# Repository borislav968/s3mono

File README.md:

# Устройство согласования ЭСУД SECU-3 c моновпрысками VAG

ЭСУД SECU-3 поддерживает использование регуляторов холостого хода на основе шагового привода или электромагнита (ШИМ). Моновпрыск Bosch, применявшийся на автомобилях VAG, использует регулятор на основе коллекторного электродвигателя с обратной связью по датчику положения дроссельной заслонки, и не имеет отдельного канала холостого хода.
Для управления этим регулятором, а также согласования сигнала положения дросселя, и предназначено это устройство. Также здесь есть драйвер низкоомной форсунки.

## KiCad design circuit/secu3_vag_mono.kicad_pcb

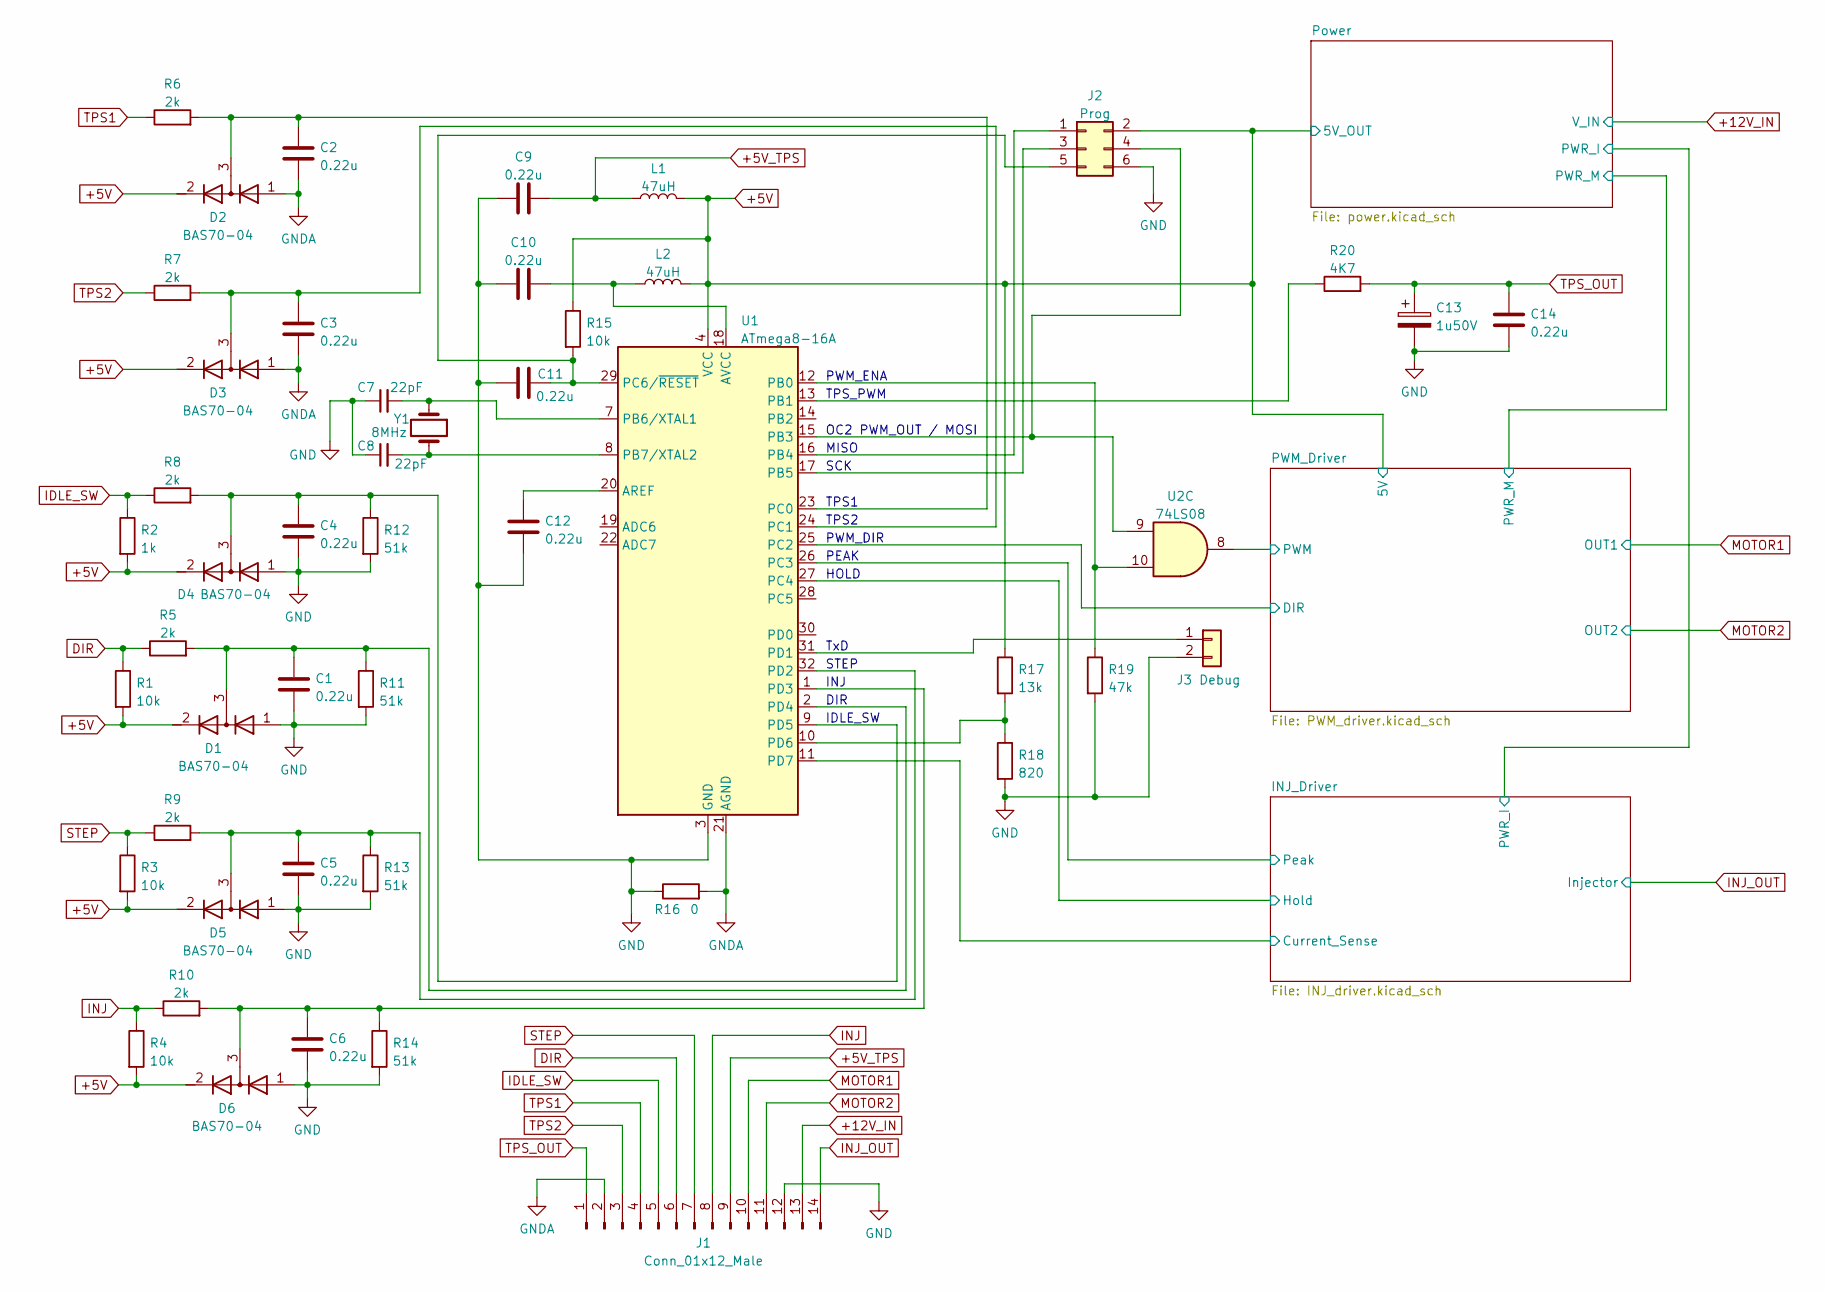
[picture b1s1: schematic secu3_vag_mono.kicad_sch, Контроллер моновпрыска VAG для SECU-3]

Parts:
C1, C2, C3, C4, C5, C6, C9, C10, C11, C12, C14: 0.22u; C_1206_3216Metric
C7, C8: 22pF; C_1206_3216Metric
C13: 1u50V; CP_Elec_4x5.4
D1, D2, D3, D4, D5, D6: BAS70-04; SOT-23
J1: Conn_01x12_Male; Molex_SPOX_5268-14A_1x14_P2.50mm_Horizontal
J2: Prog; PinHeader_2x03_P2.54mm_Vertical
J3: Debug; PinHeader_1x02_P2.54mm_Vertical
L1, L2: 47uH; L_1812_4532Metric
R1, R3, R4, R15: 10k; R_1206_3216Metric
R2: 1k; R_1206_3216Metric
R5, R6, R7, R8, R9, R10: 2k; R_1206_3216Metric
R11, R12, R13, R14: 51k; R_1206_3216Metric
R16: 0; R_1206_3216Metric
R17: 13k; R_1206_3216Metric
R18: 820; R_1206_3216Metric
R19: 47k; R_1206_3216Metric
R20: 4K7; R_1206_3216Metric
U1: ATmega8-16A; TQFP-32_7x7mm_P0.8mm
U2: 74LS08; SOIC-14_3.9x8.7mm_P1.27mm
Y1: 8MHz; Crystal_SMD_HC49-SD

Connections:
+5V: D1.2 (K), D2.2 (K), D3.2 (K), D4.2 (K), D5.2 (K), D6.2 (K), J2.2, L1.2, L2.2, R1.2, R2.2, R3.2, R4.2, R15.1, R17.1, U1.4 (VCC), U1.6 (VCC); also elsewhere on the board
+5V_TPS: C9.2, J1.9, L1.1
+12V_IN: J1.13; also elsewhere on the board
/INJ_Driver/Current_Sense: U1.11 (PD7); also elsewhere on the board
/INJ_Driver/Hold: U1.27 (PC4); also elsewhere on the board
/INJ_Driver/Peak: U1.26 (PC3); also elsewhere on the board
/PWM_Driver/DIR: U1.25 (PC2); also elsewhere on the board
/PWM_Driver/PWM: U2.8; also elsewhere on the board
DIR: J1.6, R1.1, R5.1
GND: C1.2, C4.2, C5.2, C6.2, C7.1, C8.1, C9.1, C10.1, C11.1, C12.1, C13.2, C14.2, D1.1 (A), D4.1 (A), D5.1 (A), D6.1 (A), J1.12, J2.6, J3.2, R11.2, R12.2, R13.2, R14.2, R16.1, R18.2, R19.2, U1.3 (GND), U1.5 (GND); also elsewhere on the board
GNDA: C2.2, C3.2, D2.1 (A), D3.1 (A), J1.2, R16.2, U1.21 (AGND)
IDLE_SW: J1.5, R2.1, R8.1
INJ: J1.8, R4.1, R10.1
INJ_OUT: J1.14; also elsewhere on the board
MOTOR1: J1.10; also elsewhere on the board
MOTOR2: J1.11; also elsewhere on the board
unnamed: C1.1, D1.3 (common), R5.2, R11.1, U1.2 (PD4)
unnamed: C2.1, D2.3 (common), R6.2, U1.23 (PC0)
unnamed: C3.1, D3.3 (common), R7.2, U1.24 (PC1)
unnamed: C4.1, D4.3 (common), R8.2, R12.1, U1.9 (PD5)
unnamed: C5.1, D5.3 (common), R9.2, R13.1, U1.32 (PD2)
unnamed: C6.1, D6.3 (common), R10.2, R14.1, U1.1 (PD3)
unnamed: C7.2, U1.7 (PB6/XTAL1), Y1.1
unnamed: C8.2, U1.8 (PB7/XTAL2), Y1.2
unnamed: C10.2, L2.1, U1.18 (AVCC)
unnamed: C11.2, J2.5, R15.2, U1.29 (PC6/~RESET)
unnamed: C12.2, U1.20 (AREF)
unnamed: J2.1, U1.16 (PB4)
unnamed: J2.3, U1.17 (PB5)
unnamed: J2.4, U1.15 (PB3), U2.9
unnamed: J3.1, U1.31 (PD1)
unnamed: R17.2, R18.1, U1.10 (PD6)
unnamed: R19.1, U1.12 (PB0), U2.10
unnamed: R20.1, U1.13 (PB1)
STEP: J1.7, R3.1, R9.1
TPS1: J1.4, R6.1
TPS2: J1.3, R7.1
TPS_OUT: C13.1, C14.1, J1.1, R20.2

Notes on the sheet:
MISO
SCK
STEP
TxD
TPS2
TPS_PWM
PWM_DIR
PEAK
IDLE_SW
HOLD
DIR
INJ
PWM_ENA
OC2 PWM_OUT / MOSI
TPS1

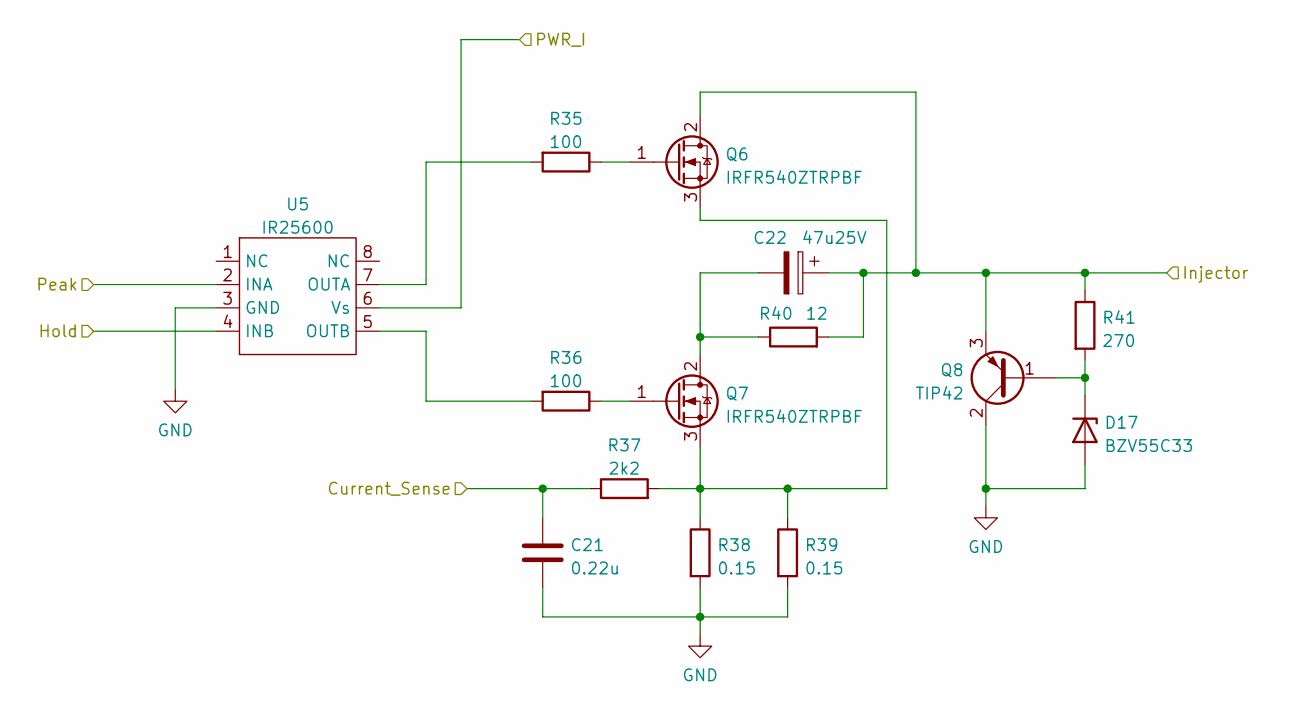
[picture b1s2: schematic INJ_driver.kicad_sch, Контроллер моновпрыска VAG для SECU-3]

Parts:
C21: 0.22u; C_1206_3216Metric
C22: 47u25V; CP_Elec_6.3x5.4
D17: BZV55C33; D_MiniMELF
Q6, Q7: IRFR540ZTRPBF; TO-252-3_TabPin2
Q8: TIP42; TO-220-3_Vertical
R35, R36: 100; R_1206_3216Metric
R37: 2k2; R_1206_3216Metric
R38, R39: 0.15; R_1206_3216Metric
R40: 12; R_Axial_Power_L25.0mm_W9.0mm_P30.48mm
R41: 270; R_1206_3216Metric
U5: IR25600; SOIC-8_3.9x4.9mm_P1.27mm

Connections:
/INJ_Driver/Current_Sense: C21.1, R37.1; also elsewhere on the board
/INJ_Driver/Hold: U5.4 (INB); also elsewhere on the board
/INJ_Driver/PWR_I: U5.6 (Vs); also elsewhere on the board
/INJ_Driver/Peak: U5.2 (INA); also elsewhere on the board
GND: C21.2, D17.2 (A), Q8.2 (C), R38.2, R39.2, U5.3 (GND); also elsewhere on the board
INJ_OUT: C22.1, Q6.2 (D), Q8.3 (E), R40.2, R41.1; also elsewhere on the board
unnamed: C22.2, Q7.2 (D), R40.1
unnamed: D17.1 (K), Q8.1 (B), R41.2
unnamed: Q6.1 (G), R35.1
unnamed: Q6.3 (S), Q7.3 (S), R37.2, R38.1, R39.1
unnamed: Q7.1 (G), R36.1
unnamed: R35.2, U5.7 (OUTA)
unnamed: R36.2, U5.5 (OUTB)

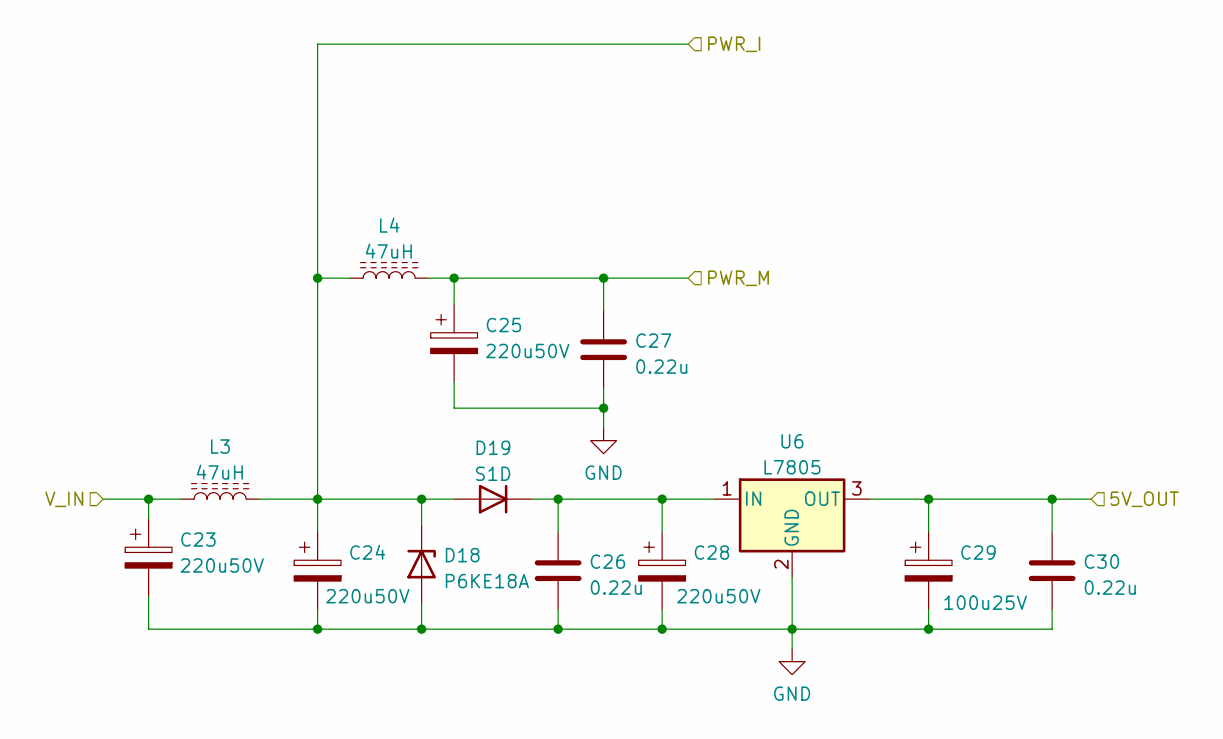
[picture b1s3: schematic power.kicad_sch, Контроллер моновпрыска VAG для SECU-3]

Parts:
C23, C24, C25, C28: 220u50V; CP_Elec_10x10.5
C26, C27, C30: 0.22u; C_1206_3216Metric
C29: 100u25V; CP_Elec_6.3x7.7
D18: P6KE18A; D_DO-15_P3.81mm_Vertical_AnodeUp
D19: S1D; D_SMA
L3, L4: 47uH; L_Bourns_SRR1260
U6: L7805; TO-252-2

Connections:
+5V: C29.1, C30.1, U6.3 (OUT); also elsewhere on the board
+12V_IN: C23.1, L3.1; also elsewhere on the board
/INJ_Driver/PWR_I: C24.1, D18.1 (K), D19.2 (A), L3.2, L4.1; also elsewhere on the board
/PWM_Driver/PWR_M: C25.1, C27.1, L4.2; also elsewhere on the board
GND: C23.2, C24.2, C25.2, C26.2, C27.2, C28.2, C29.2, C30.2, D18.2 (A), U6.2 (GND); also elsewhere on the board
unnamed: C26.1, C28.1, D19.1 (K), U6.1 (IN)

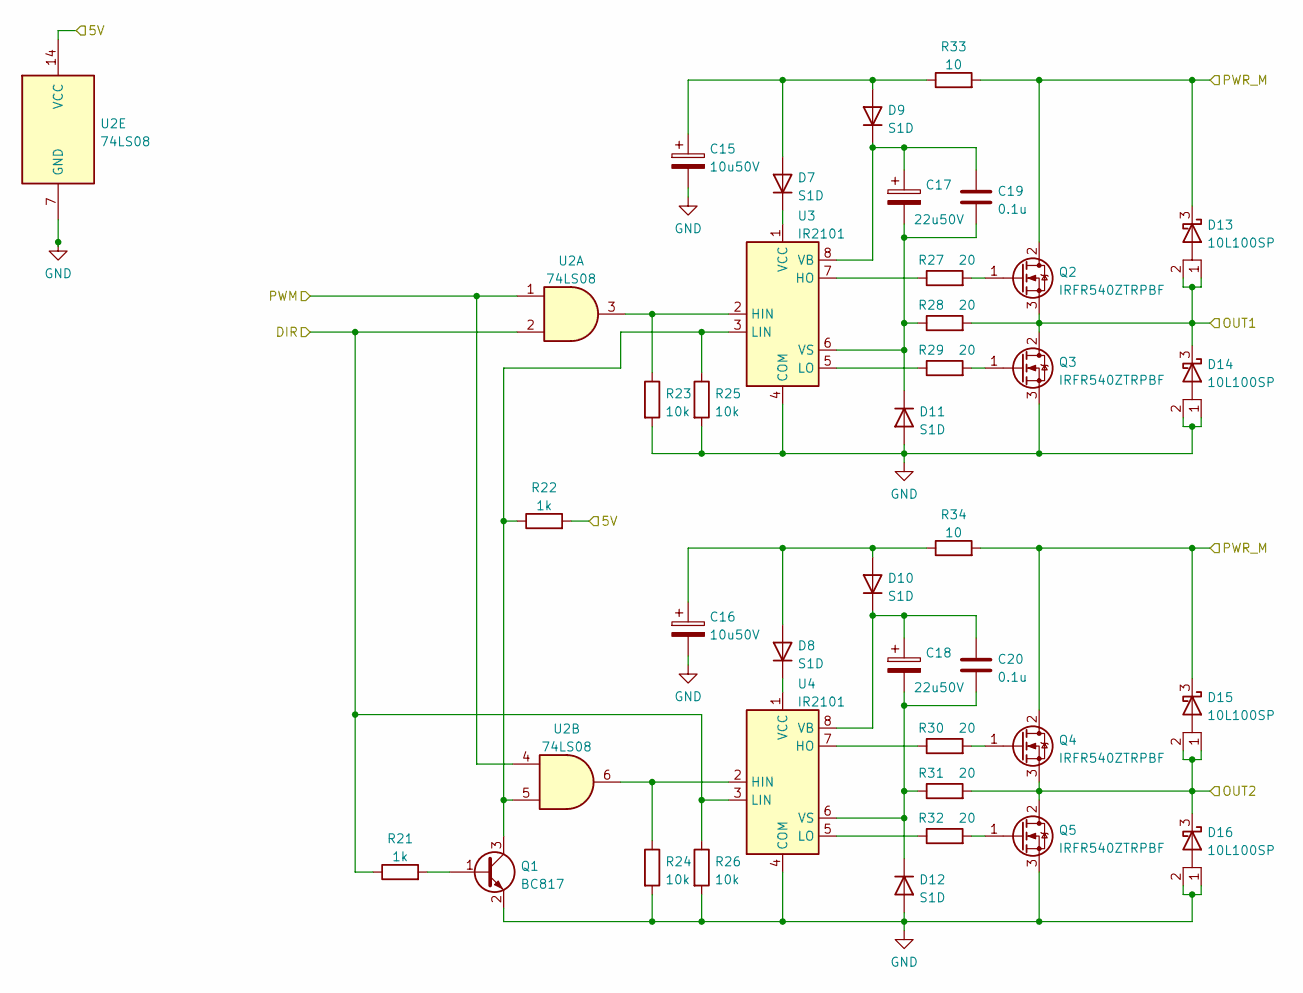
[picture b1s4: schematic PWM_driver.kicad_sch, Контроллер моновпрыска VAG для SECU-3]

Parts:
C15, C16: 10u50V; CP_Elec_6.3x5.4
C17, C18: 22u50V; CP_Elec_6.3x5.4
C19, C20: 0.1u; C_1206_3216Metric
D7, D8, D9, D10, D11, D12: S1D; D_SMA
D13, D14, D15, D16: 10L100SP; TO-277B
Q1: BC817; SOT-23
Q2, Q3, Q4, Q5: IRFR540ZTRPBF; TO-252-3_TabPin2
R21, R22: 1k; R_1206_3216Metric
R23, R24, R25, R26: 10k; R_1206_3216Metric
R27, R28, R29, R30, R31, R32: 20; R_1206_3216Metric
R33, R34: 10; R_1206_3216Metric
U2: 74LS08; SOIC-14_3.9x8.7mm_P1.27mm
U3, U4: IR2101; SOIC-8_3.9x4.9mm_P1.27mm

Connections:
+5V: R22.2, U2.14 (VCC); also elsewhere on the board
/PWM_Driver/DIR: R21.1, R26.1, U2.2, U4.3 (LIN); also elsewhere on the board
/PWM_Driver/PWM: U2.1, U2.4; also elsewhere on the board
/PWM_Driver/PWR_M: D13.3, D15.3, Q2.2 (D), Q4.2 (D), R33.2, R34.2; also elsewhere on the board
GND: C15.2, C16.2, D11.2 (A), D12.2 (A), D14.1, D14.2, D16.1, D16.2, Q1.2 (E), Q3.3 (S), Q5.3 (S), R23.2, R24.2, R25.2, R26.2, U2.7 (GND), U3.4 (COM), U4.4 (COM); also elsewhere on the board
MOTOR1: D13.1, D13.2, D14.3, Q2.3 (S), Q3.2 (D), R28.2; also elsewhere on the board
MOTOR2: D15.1, D15.2, D16.3, Q4.3 (S), Q5.2 (D), R31.2; also elsewhere on the board
unnamed: C15.1, D7.2 (A), D9.2 (A), R33.1
unnamed: C16.1, D8.2 (A), D10.2 (A), R34.1
unnamed: C17.1, C19.1, D9.1 (K), U3.8 (VB)
unnamed: C17.2, C19.2, D11.1 (K), R28.1, U3.6 (VS)
unnamed: C18.1, C20.1, D10.1 (K), U4.8 (VB)
unnamed: C18.2, C20.2, D12.1 (K), R31.1, U4.6 (VS)
unnamed: D7.1 (K), U3.1 (VCC)
unnamed: D8.1 (K), U4.1 (VCC)
unnamed: Q1.1 (B), R21.2
unnamed: Q1.3 (C), R22.1, R25.1, U2.5, U3.3 (LIN)
unnamed: Q2.1 (G), R27.2
unnamed: Q3.1 (G), R29.2
unnamed: Q4.1 (G), R30.2
unnamed: Q5.1 (G), R32.2
unnamed: R23.1, U2.3, U3.2 (HIN)
unnamed: R24.1, U2.6, U4.2 (HIN)
unnamed: R27.1, U3.7 (HO)
unnamed: R29.1, U3.5 (LO)
unnamed: R30.1, U4.7 (HO)
unnamed: R32.1, U4.5 (LO)

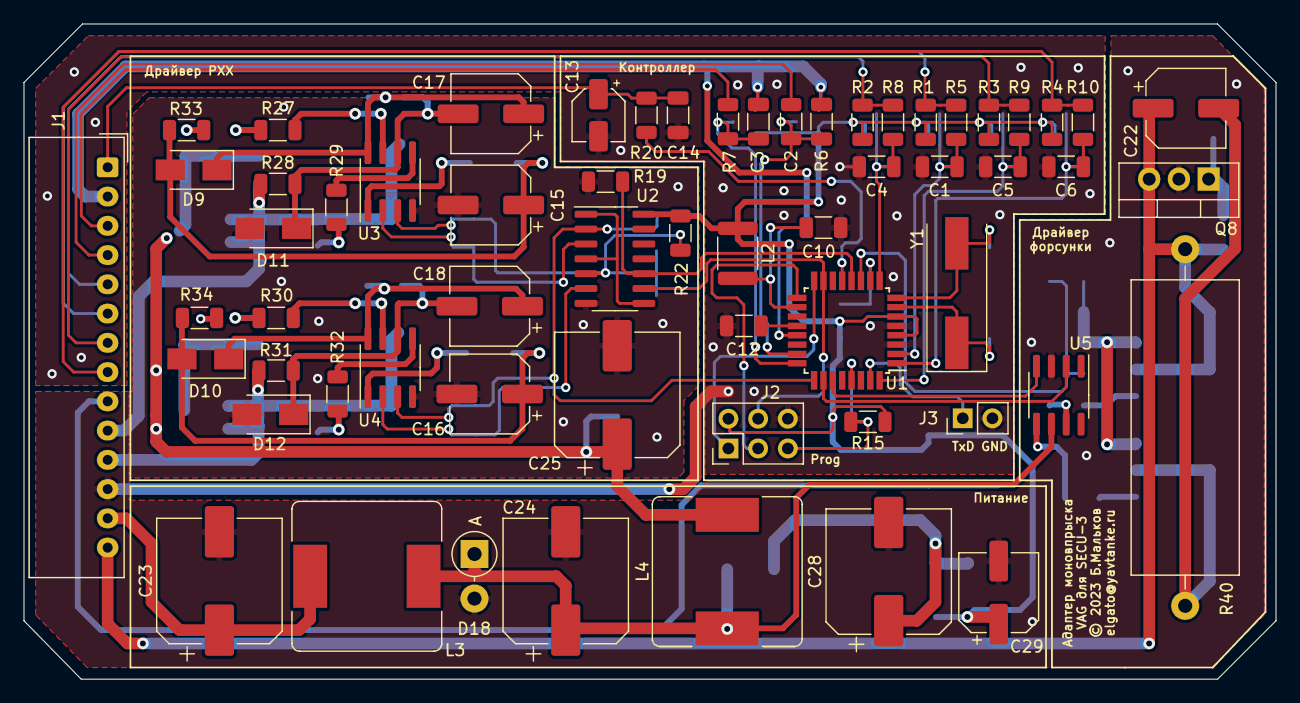
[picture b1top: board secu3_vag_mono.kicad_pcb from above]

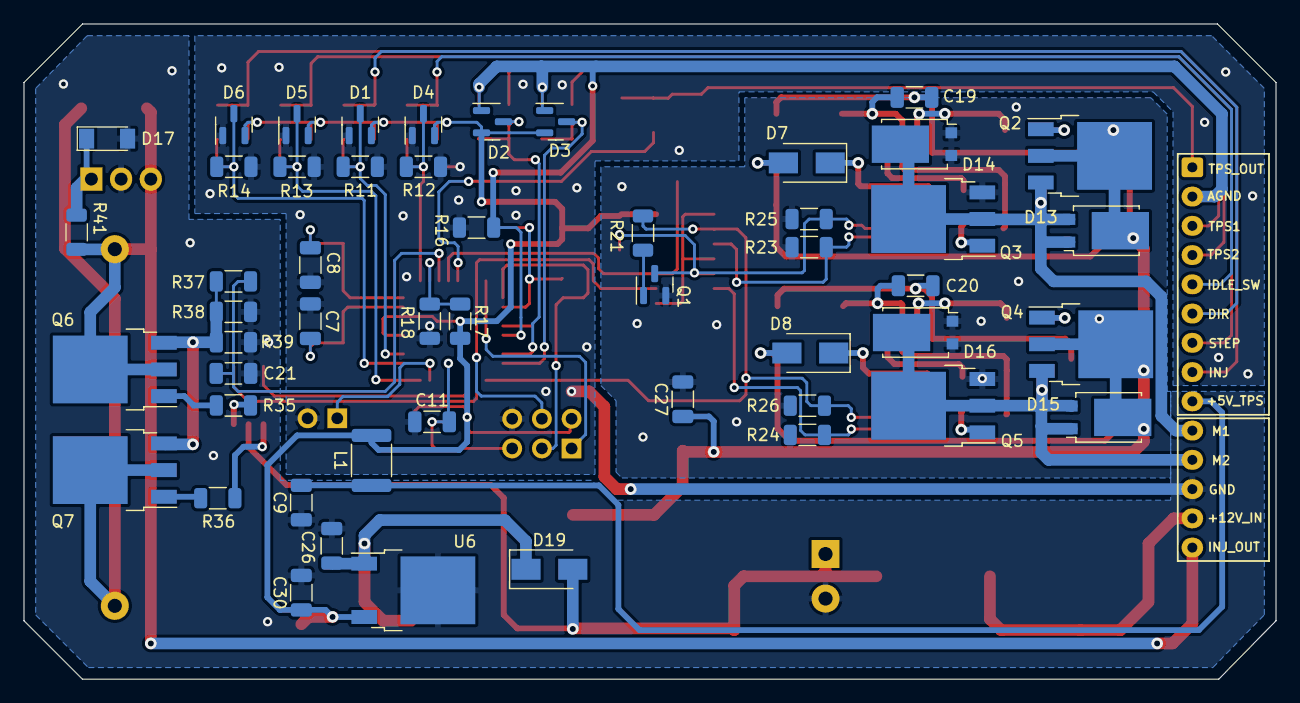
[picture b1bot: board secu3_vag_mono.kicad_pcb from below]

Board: 2 copper layers, 107.0 x 56.0 mm, 112 parts (51 on the bottom side), 68 nets.

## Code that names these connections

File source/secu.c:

#include <avr/io.h>
#include <avr/interrupt.h>

// Число шагов РХХ
uint16_t _steps_max;

// Положение РХХ в шагах, 0.._steps_max
volatile uint16_t _steps = 0;

// Настройка обмена с SECU-3
void init_secu_connection( volatile uint16_t** steps, uint16_t steps_max ) {
    
    // Настройка таймера 1 - эмуляция ДПДЗ для SECU
    DDRB |= (1<<PB1);       // PB1 - выход ШИМ-сигнала положения дросселя
    TCCR1A |= (1<<COM1A1);  // Подключение PB1 к выходу таймера 1, без инверсии
    TCCR1A |= (1<<WGM10);   // Режим таймера - ШИМ с правильной фазой, 8 бит
    OCR1A = 0;              // Скважность 0
    TCCR1B |= (1<<CS10);    // Частота 8МГц / 1 / 256 = 31.25кГц

    // INT0 (PD2) - вход шагов РХ Х от SECU-3
    MCUCR |= (1<<ISC01);    // прерывание INT0 по отрицательному фронту на входе
    GICR |= (1<<INT0);      // включить INT0
    
    // INT1 (PD3) - вход управляющего сигнала форсунки
    MCUCR |= (1<<ISC10);    // Прерывание INT1 по любому изменению логического уровня на входе
    GICR |= (1<<INT1);      // Включить INT1

    // Драйверы форсунки
    DDRC |= (1<<PC3);       // Выход на открывающий драйвер форсунки
    DDRC |= (1<<PC4);       // Выход на удерживающий драйвер форсунки

    // Настройка компаратора
    ACSR |= (1<<ACIS1);     // Срабатывание по отрицательному фронту
    ACSR |= (1<<ACIE);      // Включить прерывание компаратора    
    
    _steps_max = steps_max; // число шагов РХХ
    
    *steps = &_steps;       // привязка указателя на текущее число шагов
    
}


// Положение ДПДЗ для SECU
// value 0..255 соответствует напряжению 0..5В на выходе
void secu_set_tps (uint8_t value) {
    OCR1A = value;
}

// Обработчик прерывания INT0
// сигнал шагов РХХ
ISR (INT0_vect) {
    
    if (PIND & (1<<PD4)) {                  // высокий уровень на входе DIR (PD4) - уменьшение
        if (_steps) _steps--;               // уменьшить на 1, если не 0
    } else {                                // низкий уровень на входе DIR - увеличение
        if (_steps < _steps_max) _steps++;  // увеличить на 1, если меньше _steps_max
    }
    
}

// Обработчик прерывания INT1
// сигнал управления форсункой

ISR (INT1_vect) {
    if (PIND & (1<<PD3))                    // Если на входе 1 (вход инверсный),
        PORTC &= ~((1<<PC3) | (1<<PC4));    // отключить оба драйвера форсунки,
    else
        PORTC |= (1<<PC3) | (1<<PC4);       // иначе включить их.
}


// Обработчик прерывания от компаратора
// ток форсунки достиг 4А

ISR (ANA_COMP_vect) {
    PORTC &= ~(1<<PC3);  // отключить открывающий драйвер, оставив только удерживающий.
}

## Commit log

2024-12-26 Readme
2024-12-26 Исходные тексты
2024-12-26 Схема платы
2024-12-26 Определение имени проекта

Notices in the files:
circuit/secu3_vag_mono.kicad_pcb:
© 2023 Б.Мальков
